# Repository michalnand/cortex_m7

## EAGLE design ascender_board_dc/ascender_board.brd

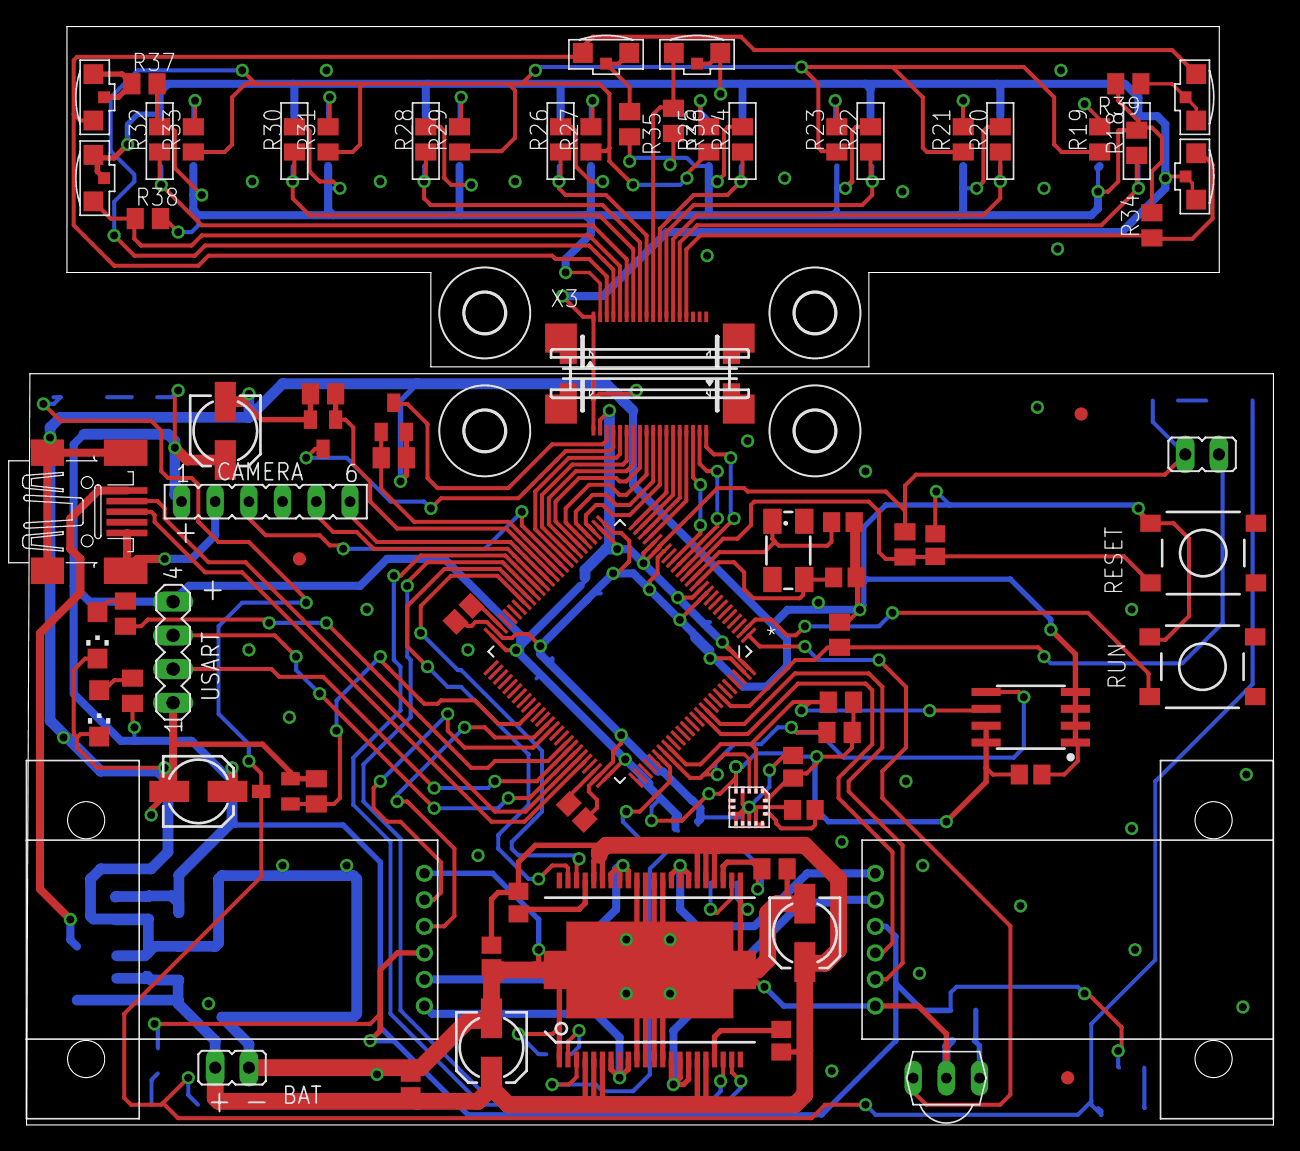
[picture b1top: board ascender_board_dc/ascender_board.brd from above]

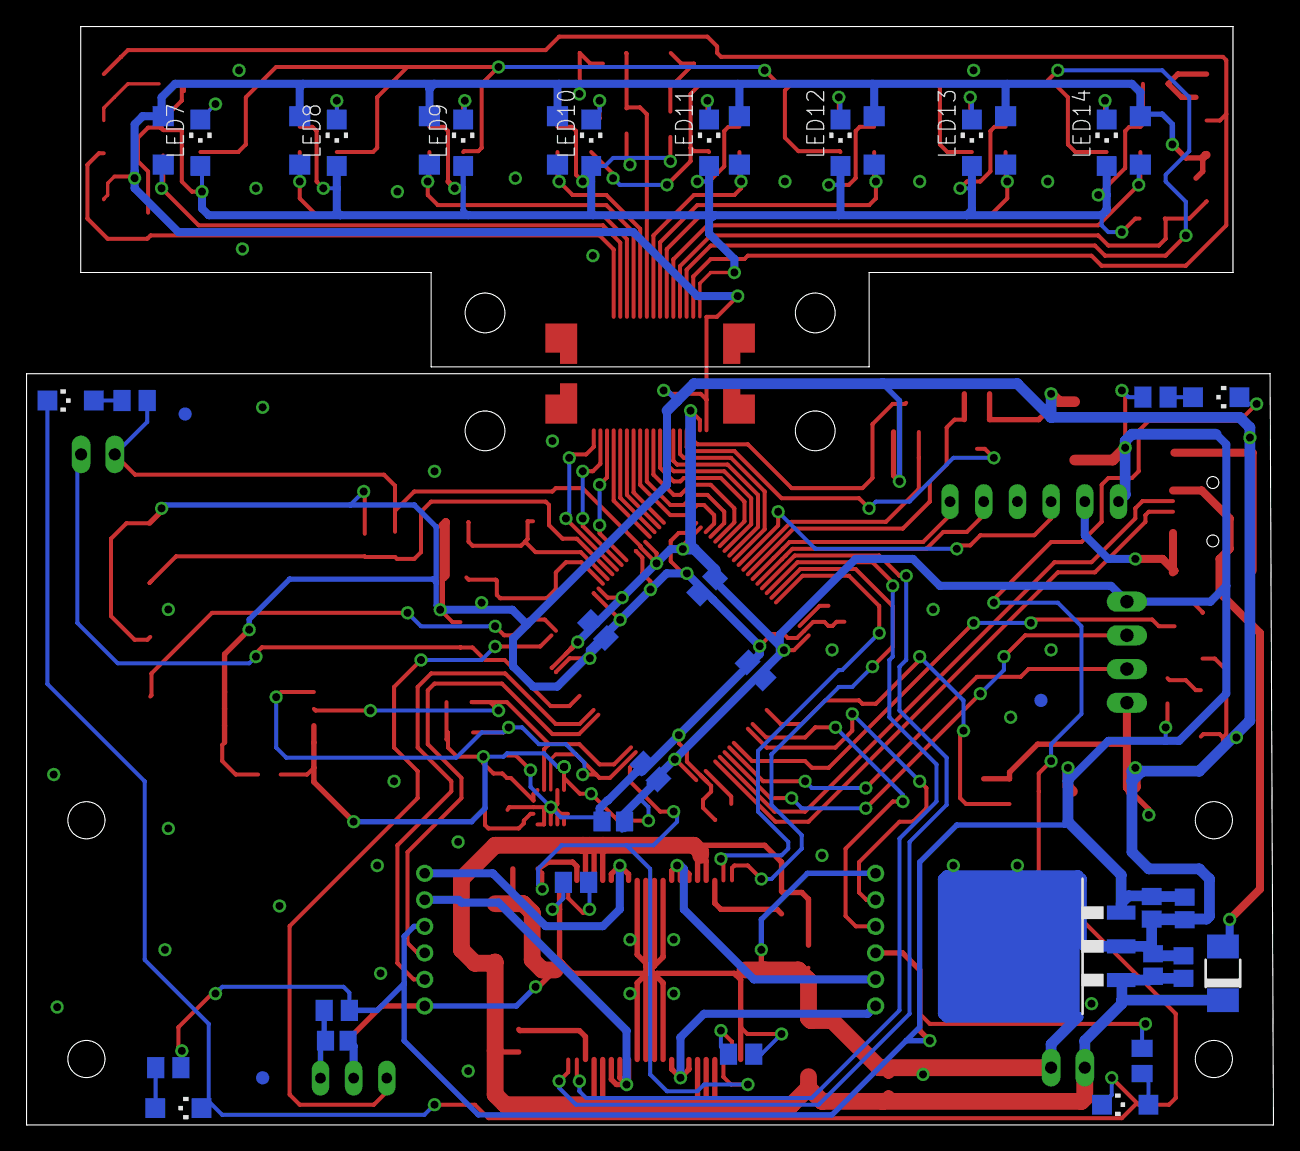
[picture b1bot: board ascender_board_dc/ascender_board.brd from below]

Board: 2 copper layers, 94.0 x 82.8 mm, 125 parts (42 on the bottom side), 91 nets.

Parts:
BAT: LiPol; JP1
BOOT: JP1
C1: C0805
C2: 18p; C0805
C3, C6, C7, C8, C9, C10, C12, C15, C16, C17, C18, C19, C23, C26: 100n; C0805
C4, C5: 2.2uF; C0805
C11, C13, C25: 10uF; C0805
C14: 10n; C0805
C20, C21, C22, C24: 153CLV-0505
CAMERA: FE06
D1: DO-214AC
H1, H2, H3, H4: MOUNT-HOLE3.0; 3,0
IC1: LM2937; TO263-3
IC2: MC33932; HSOP44
LED1, LED2, LED3, LED4, LED5, LED6, LED7, LED8, LED9, LED10, LED11, LED12, LED13, LED14: CHIPLED_1206
Q1: 8MHz; CTS406
Q2, Q3, Q4: BSS123; SOT23
R1, R2, R3, R4, R5, R6, R7, R8, R9, R10, R11, R12, R18, R20, R22, R24, R26, R28, R30, R32, R34, R36, R38: 4k7; M0805
R13, R14, R15, R16, R19, R21, R23, R25, R27, R29, R31, R33: 330; M0805
R17, R35, R37, R39: 22; M0805
RESET: DTSM-6
RUN: DTSM-6
U1: STM32F722XX; QFP50P1600X1600X160-100N
U2: I2C EEPROM; SO08-EIAJ
U$1, U$10: POLOLU_GEAR_MOTORPOLO; POLOLU_GEAR_MOTOR
U$2: ST_L3GD20H; ST_LGA16L
U$3, U$4, U$5, U$6, U$7, U$8: FIDUCIAL; FIDUCIAL_1MM
U$9: TSOP4830; TSOP18XX
U$11, U$14, U$15, U$16, U$17, U$18, U$19, U$20: SFH3710
U$12, U$29, U$31: KPA3010
U$13, U$30, U$32: KPA3010_EM; KPA3010
USART: MA04-1
X2, X3: 52745-1890
X4: MINI-USB-SCHIELD-32005-201; 32005-201

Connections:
+3V3: BOOT.2, C6.1, C7.1, C8.1, C9.1, C12.1, C13.1, C15.1, C16.1, C22.+, C24.+, C26.1, CAMERA.1, IC1.3, LED7.A, LED8.A, LED9.A, LED10.A, LED11.A, LED12.A, LED13.A, LED14.A, R1.2, R4.2, R5.2, R6.2, R13.2, R14.2, R15.2, R16.2, R17.2, R18.2, R20.2, R22.2, R24.2, R26.2, R28.2, R30.2, R32.2, R34.2, R35.2, R36.2, R37.2, R38.2, R39.2, U1.11, U1.20, U1.21, U1.27, U1.50, U1.75, U1.100, U2.7, U2.8, U$1.P$3, U$2.P$1, U$2.P$5, U$2.P$16, U$10.P$3, USART.4, X2.17, X3.2
ADC0: U1.22, X2.4
ADC1: U1.23, X2.5
ADC1_S: R18.1, U$11.P$2, X3.14
ADC2: U1.24, X2.6
ADC2_S: R20.1, U$14.P$2, X3.13
ADC3: U1.25, X2.7
ADC3_S: R22.1, U$15.P$2, X3.12
ADC4: U1.28, X2.8
ADC4_S: R24.1, U$16.P$2, X3.11
ADC5: U1.29, X2.9
ADC6: U1.30, X2.10
ADC6_S: R26.1, U$17.P$2, X3.9
ADC7: U1.31, X2.11
ADC7_S: R28.1, U$18.P$2, X3.8
ADC8: U1.32, X2.12
ADC8_S: R30.1, U$19.P$2, X3.7
ADC9: U1.33, X2.13
ADC9_S: R32.1, U$20.P$2, X3.6
ADC10: U1.34, X2.14
ADC11: CAMERA.3, U1.35
BOOT: BOOT.1, R2.2, U1.94
CAM_CLK: CAMERA.5, U1.39
CAM_SI: CAMERA.6, U1.38
ENC_A_LEFT: U1.63, U$10.P$4
ENC_A_RIGHT: U1.90, U$1.P$4
ENC_B_LEFT: U1.64, U$10.P$5
ENC_B_RIGHT: U1.91, U$1.P$5
FRONT_GPIO: U1.17, X2.3
FRONT_SCL: U1.15, X2.1
FRONT_SDA: U1.16, X2.2
GND: BAT.1, C1.2, C2.2, C3.2, C4.2, C5.1, C6.2, C7.2, C8.2, C9.2, C10.2, C11.2, C12.2, C13.2, C14.2, C15.2, C16.2, C19.2, C20.-, C21.-, C22.-, C23.2, C24.-, C25.2, C26.2, CAMERA.2, IC1.2, IC2.1, IC2.10, IC2.11, IC2.12, IC2.13, IC2.23, IC2.32, IC2.33, IC2.34, IC2.35, IC2.EH@1, IC2.EH@2, IC2.EH@3, LED1.C, LED2.C, Q2.2, Q3.2, Q4.2, R2.1, R7.1, R8.1, R9.2, R10.1, R11.1, R12.1, RESET.1, RUN.1, U1.10, U1.19, U1.26, U1.49, U1.74, U1.99, U2.1, U2.2, U2.3, U2.4, U$1.P$6, U$2.P$4, U$2.P$8, U$2.P$9, U$2.P$10, U$2.P$11, U$2.P$12, U$2.P$13, U$2.P$15, U$9.GND, U$10.P$6, U$11.P$1, U$12.P$2_EM, U$12.P$3-NC, U$14.P$1, U$15.P$1, U$16.P$1, U$17.P$1, U$18.P$1, U$19.P$1, U$20.P$1, U$29.P$2_EM, U$29.P$3-NC, U$31.P$2_EM, U$31.P$3-NC, USART.1, X2.18, X3.1, X4.5, X4.M1, X4.M2, X4.M3, X4.M4
IR_A: Q2.3, X2.15
IR_A_CONTROLL: Q2.1, R10.2, U1.37
IR_A_S: R19.1, R21.1, R23.1, R25.1, R27.1, R29.1, R31.1, R33.1, X3.4
IR_B: Q3.3, X2.16
IR_B_CONTROLL: Q3.1, R11.2, U1.36
IR_B_S: U$13.P$1_COL, U$30.P$1_COL, U$32.P$1_COL, X3.3
IR_FRONT_S: R36.1, U$29.P$1_COL, X3.10
IR_LEFT_S: R38.1, U$31.P$1_COL, X3.5
IR_REMOTE: U1.1, U$9.OUT
IR_RIGHT_S: R34.1, U$12.P$1_COL, X3.15
KEY: RUN.3, U1.2
LED: R3.2, U1.67
LED_BACK: Q4.1, R12.2, U1.60
MOTOR_ENABLE: IC2.3, IC2.25, R7.2, U1.81
unnamed: C2.1, Q1.3, U1.12
unnamed: C1.1, Q1.1, U1.13
unnamed: C4.1, U1.48
unnamed: C5.2, U1.73
unnamed: LED1.A, R3.1
unnamed: C14.1, U$2.P$14
unnamed: IC2.7, IC2.8, IC2.9, U$10.P$1
unnamed: IC2.36, IC2.37, IC2.38, U$10.P$2
unnamed: IC2.14, IC2.15, IC2.16, U$1.P$2
unnamed: IC2.29, IC2.30, IC2.31, U$1.P$1
unnamed: LED2.A, R6.1
unnamed: C17.2, IC2.41
unnamed: IC2.2, R8.2
unnamed: C18.1, IC2.19
unnamed: IC2.24, R9.1
unnamed: LED3.C, LED4.C, LED5.C, LED6.C, Q4.3
unnamed: LED3.A, R13.1
unnamed: D1.A, X4.1
unnamed: LED4.A, R14.1
unnamed: C25.1, R17.1, U$9.VCC
unnamed: LED5.A, R15.1
unnamed: LED8.C, R21.2
unnamed: LED6.A, R16.1
unnamed: LED7.C, R19.2
unnamed: LED9.C, R23.2
unnamed: LED10.C, R25.2
unnamed: LED11.C, R27.2
unnamed: LED12.C, R29.2
unnamed: LED13.C, R31.2
unnamed: LED14.C, R33.2
unnamed: R37.1, U$30.P$2_EM, U$30.P$3-NC
unnamed: R35.1, U$13.P$2_EM, U$13.P$3-NC
unnamed: R39.1, U$32.P$2_EM, U$32.P$3-NC
PWM_A_LEFT: IC2.43, U1.42
PWM_A_RIGHT: IC2.21, U1.40
PWM_B_LEFT: IC2.42, U1.43
PWM_B_RIGHT: IC2.20, U1.41
RESET: C3.1, R1.1, RESET.3, U1.14
SCL: R5.1, U1.83, U2.6, U$2.P$2
SDA: R4.1, U1.82, U2.5, U$2.P$3
USART1_RX: U1.69, USART.3
USART1_TX: U1.68, USART.2
USBDM: U1.70, X4.2
USBDP: U1.71, X4.3
VCC: BAT.2, C10.1, C11.1, C17.1, C18.2, C19.1, C20.+, C21.+, C23.1, D1.C, IC1.1, IC2.4, IC2.5, IC2.6, IC2.17, IC2.18, IC2.26, IC2.27, IC2.28, IC2.39, IC2.40

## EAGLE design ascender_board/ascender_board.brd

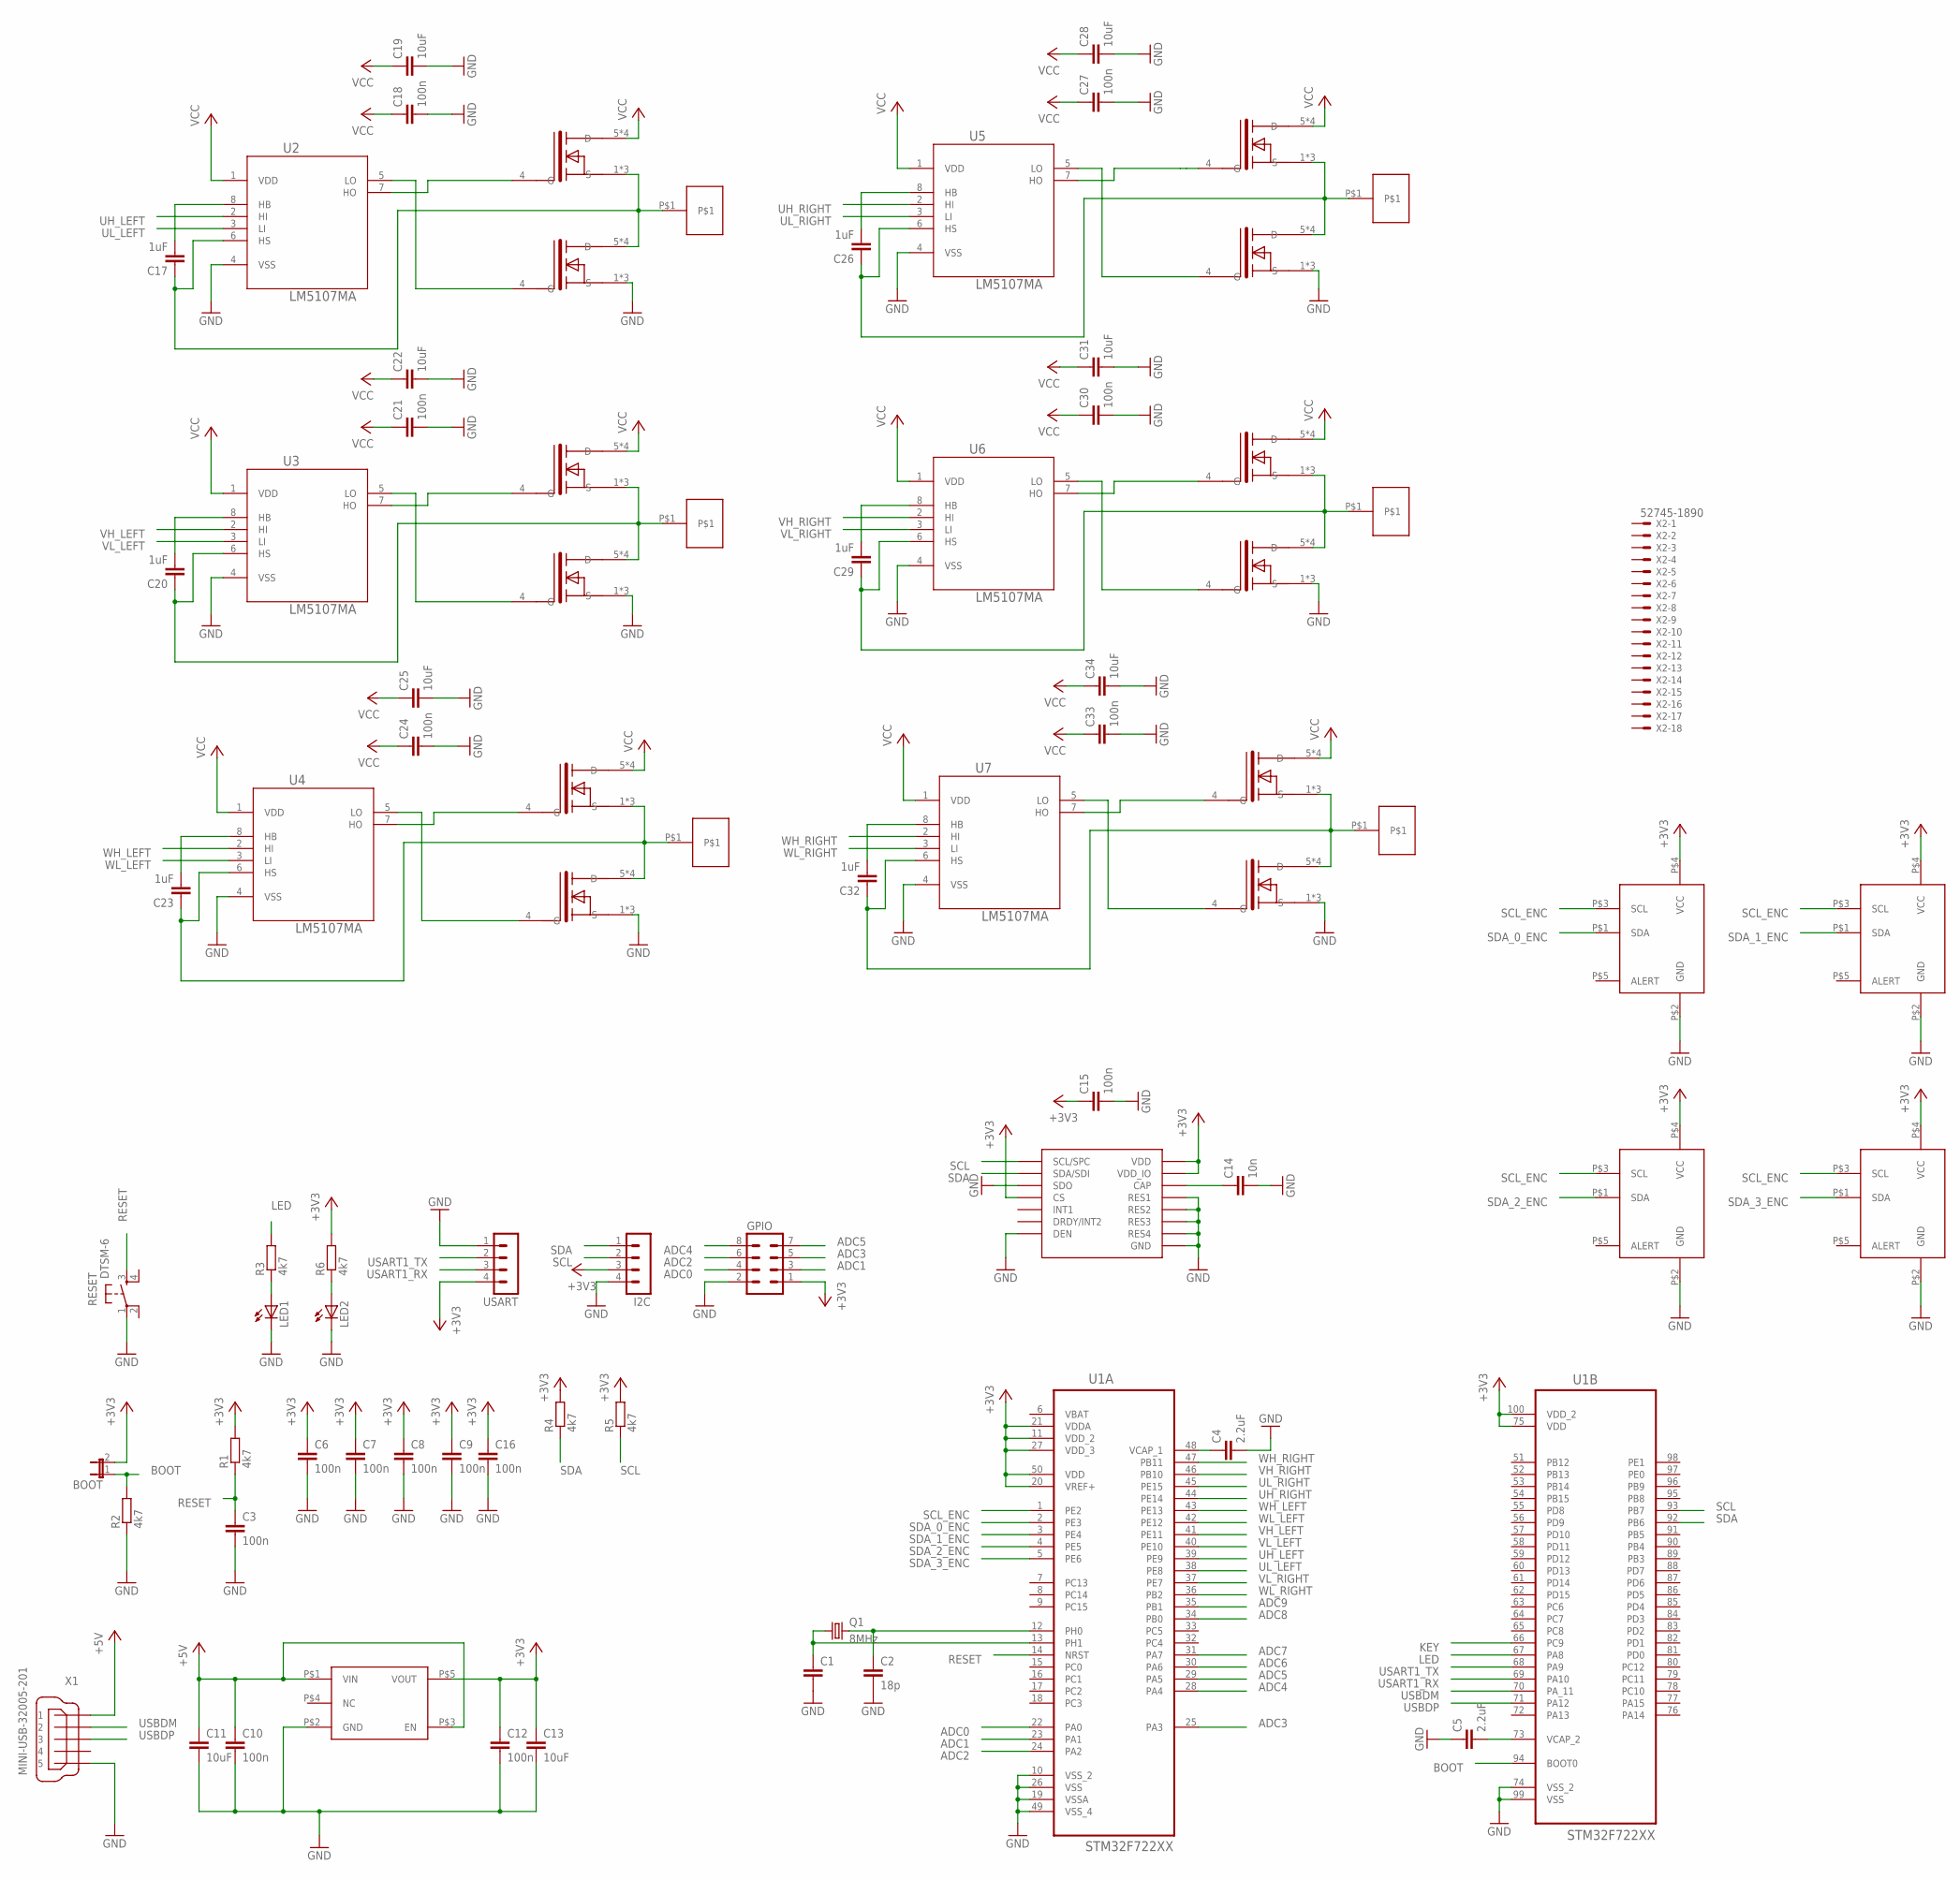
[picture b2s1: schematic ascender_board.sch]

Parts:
BOOT: JP1E; JP1
C1: C-EUC0805; C0805
C2: 18p; C0805
C3, C6, C7, C8, C9, C10, C12, C15, C16, C18, C21, C24, C27, C30, C33: 100n; C0805
C4, C5: 2.2uF; C0805
C11, C13, C19, C22, C25, C28, C31, C34: 10uF; C0805
C14: 10n; C0805
C17, C20, C23, C26, C29, C32: 1uF; C0805
GPIO: MA04-2
I2C: MA04-1
LED1, LED2: LEDCHIPLED_1206; CHIPLED_1206
Q1: 8MHz; CTS406
R1, R2, R3, R4, R5, R6: 4k7; M0805
RESET: DTSM-6
U1: STM32F722XX; QFP50P1600X1600X160-100N
U2, U3, U4, U5, U6, U7: LM5107MA; SOIC127P620X175-8N
U$1: MIC5504-3.3Y; SOT23-5
U$2: ST_L3GD20H; ST_LGA16L
U$4, U$5, U$7, U$8, U$10, U$11, U$13, U$14, U$16, U$17, U$19, U$20: IRFH7004; PQFN5X6
U$6, U$9, U$12, U$15, U$18, U$21: BLDC_MOTOR_PIN
U$22, U$23, U$24, U$25: SI7210; SOT23-5
USART: MA04-1
X1: MINI-USB-32005-201; 32005-201
X2: 52745-1890

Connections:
+3V3: BOOT.2, C6.1, C7.1, C8.1, C9.1, C12.1, C13.1, C15.1, C16.1, GPIO.1, I2C.3, R1.2, R4.2, R5.2, R6.2, U1.11 (VDD_2), U1.20 (VREF+), U1.21 (VDDA), U1.27 (VDD_3), U1.50 (VDD), U1.75 (VDD), U1.100 (VDD_2), U$1.P$5 (VOUT), U$2.P$1 (VDD_IO), U$2.P$5 (CS), U$2.P$16 (VDD), U$22.P$4 (VCC), U$23.P$4 (VCC), U$24.P$4 (VCC), U$25.P$4 (VCC), USART.4
+5V: C10.1, C11.1, U$1.P$1 (VIN), U$1.P$3 (EN), X1.1
ADC0: GPIO.4, U1.22 (PA0)
ADC1: GPIO.3, U1.23 (PA1)
ADC2: GPIO.6, U1.24 (PA2)
ADC3: GPIO.5, U1.25 (PA3)
ADC4: GPIO.8, U1.28 (PA4)
ADC5: GPIO.7, U1.29 (PA5)
ADC6: U1.30 (PA6)
ADC7: U1.31 (PA7)
ADC8: U1.34 (PB0)
ADC9: U1.35 (PB1)
BOOT: BOOT.1, R2.2, U1.94 (BOOT0)
GND: C1.2, C2.2, C3.2, C4.2, C5.1, C6.2, C7.2, C8.2, C9.2, C10.2, C11.2, C12.2, C13.2, C14.2, C15.2, C16.2, C18.2, C19.2, C21.2, C22.2, C24.2, C25.2, C27.2, C28.2, C30.2, C31.2, C33.2, C34.2, GPIO.2, I2C.4, LED1.C, LED2.C, R2.1, RESET.1, U1.10 (VSS_2), U1.19 (VSSA), U1.26 (VSS), U1.49 (VSS_4), U1.74 (VSS_2), U1.99 (VSS), U2.4 (VSS), U3.4 (VSS), U4.4 (VSS), U5.4 (VSS), U6.4 (VSS), U7.4 (VSS), U$1.P$2 (GND), U$2.P$4 (SDO), U$2.P$8 (DEN), U$2.P$9 (RES1), U$2.P$10 (RES2), U$2.P$11 (RES3), U$2.P$12 (GND), U$2.P$13 (GND), U$2.P$15 (RES4), U$5.1 (S), U$5.2 (S), U$5.3 (S), U$8.1 (S), U$8.2 (S), U$8.3 (S), U$11.1 (S), U$11.2 (S), U$11.3 (S), U$14.1 (S), U$14.2 (S), U$14.3 (S), U$17.1 (S), U$17.2 (S), U$17.3 (S), U$20.1 (S), U$20.2 (S), U$20.3 (S), U$22.P$2 (GND), U$23.P$2 (GND), U$24.P$2 (GND), U$25.P$2 (GND), USART.1, X1.5
KEY: U1.66 (PC9)
LED: R3.2, U1.67 (PA8)
unnamed: C2.1, Q1.3 (2), U1.12 (PH0)
unnamed: C1.1, Q1.1, U1.13 (PH1)
unnamed: C4.1, U1.48 (VCAP_1)
unnamed: C5.2, U1.73 (VCAP_2)
unnamed: LED1.A, R3.1
unnamed: C14.1, U$2.P$14 (CAP)
unnamed: U3.5 (LO), U$8.4 (G)
unnamed: U2.5 (LO), U$5.4 (G)
unnamed: U2.7 (HO), U$4.4 (G)
unnamed: LED2.A, R6.1
unnamed: U3.7 (HO), U$7.4 (G)
unnamed: C17.2, U2.8 (HB)
unnamed: C17.1, U2.6 (HS), U$4.1 (S), U$4.2 (S), U$4.3 (S), U$5.5 (D), U$5.6 (D), U$5.7 (D), U$5.8 (D), U$6.P$1
unnamed: C20.2, U3.8 (HB)
unnamed: C20.1, U3.6 (HS), U$7.1 (S), U$7.2 (S), U$7.3 (S), U$8.5 (D), U$8.6 (D), U$8.7 (D), U$8.8 (D), U$9.P$1
unnamed: U4.5 (LO), U$11.4 (G)
unnamed: U4.7 (HO), U$10.4 (G)
unnamed: C23.2, U4.8 (HB)
unnamed: C23.1, U4.6 (HS), U$10.1 (S), U$10.2 (S), U$10.3 (S), U$11.5 (D), U$11.6 (D), U$11.7 (D), U$11.8 (D), U$12.P$1
unnamed: U5.5 (LO), U$14.4 (G)
unnamed: U5.7 (HO), U$13.4 (G)
unnamed: C26.2, U5.8 (HB)
unnamed: C26.1, U5.6 (HS), U$13.1 (S), U$13.2 (S), U$13.3 (S), U$14.5 (D), U$14.6 (D), U$14.7 (D), U$14.8 (D), U$15.P$1
unnamed: U6.5 (LO), U$17.4 (G)
unnamed: U6.7 (HO), U$16.4 (G)
unnamed: C29.2, U6.8 (HB)
unnamed: C29.1, U6.6 (HS), U$16.1 (S), U$16.2 (S), U$16.3 (S), U$17.5 (D), U$17.6 (D), U$17.7 (D), U$17.8 (D), U$18.P$1
unnamed: U7.5 (LO), U$20.4 (G)
unnamed: U7.7 (HO), U$19.4 (G)
unnamed: C32.2, U7.8 (HB)
unnamed: C32.1, U7.6 (HS), U$19.1 (S), U$19.2 (S), U$19.3 (S), U$20.5 (D), U$20.6 (D), U$20.7 (D), U$20.8 (D), U$21.P$1
RESET: C3.1, R1.1, RESET.3, U1.14 (NRST)
SCL: I2C.2, R5.1, U1.93 (PB7), U$2.P$2 (SCL/SPC)
SCL_ENC: U1.1 (PE2), U$22.P$3 (SCL), U$23.P$3 (SCL), U$24.P$3 (SCL), U$25.P$3 (SCL)
SDA: I2C.1, R4.1, U1.92 (PB6), U$2.P$3 (SDA/SDI)
SDA_0_ENC: U1.2 (PE3), U$22.P$1 (SDA)
SDA_1_ENC: U1.3 (PE4), U$23.P$1 (SDA)
SDA_2_ENC: U1.4 (PE5), U$24.P$1 (SDA)
SDA_3_ENC: U1.5 (PE6), U$25.P$1 (SDA)
UH_LEFT: U1.39 (PE9), U2.2 (HI)
UH_RIGHT: U1.44 (PE14), U5.2 (HI)
UL_LEFT: U1.38 (PE8), U2.3 (LI)
UL_RIGHT: U1.45 (PE15), U5.3 (LI)
USART1_RX: U1.69 (PA10), USART.3
USART1_TX: U1.68 (PA9), USART.2
USBDM: U1.70 (PA_11), X1.2
USBDP: U1.71 (PA12), X1.3
VBAT: U1.6 (VBAT)
VCC: C18.1, C19.1, C21.1, C22.1, C24.1, C25.1, C27.1, C28.1, C30.1, C31.1, C33.1, C34.1, U2.1 (VDD), U3.1 (VDD), U4.1 (VDD), U5.1 (VDD), U6.1 (VDD), U7.1 (VDD), U$4.5 (D), U$4.6 (D), U$4.7 (D), U$4.8 (D), U$7.5 (D), U$7.6 (D), U$7.7 (D), U$7.8 (D), U$10.5 (D), U$10.6 (D), U$10.7 (D), U$10.8 (D), U$13.5 (D), U$13.6 (D), U$13.7 (D), U$13.8 (D), U$16.5 (D), U$16.6 (D), U$16.7 (D), U$16.8 (D), U$19.5 (D), U$19.6 (D), U$19.7 (D), U$19.8 (D)
VH_LEFT: U1.41 (PE11), U3.2 (HI)
VH_RIGHT: U1.46 (PB10), U6.2 (HI)
VL_LEFT: U1.40 (PE10), U3.3 (LI)
VL_RIGHT: U1.37 (PE7), U6.3 (LI)
WH_LEFT: U1.43 (PE13), U4.2 (HI)
WH_RIGHT: U1.47 (PB11), U7.2 (HI)
WL_LEFT: U1.42 (PE12), U4.3 (LI)
WL_RIGHT: U1.36 (PB2), U7.3 (LI)

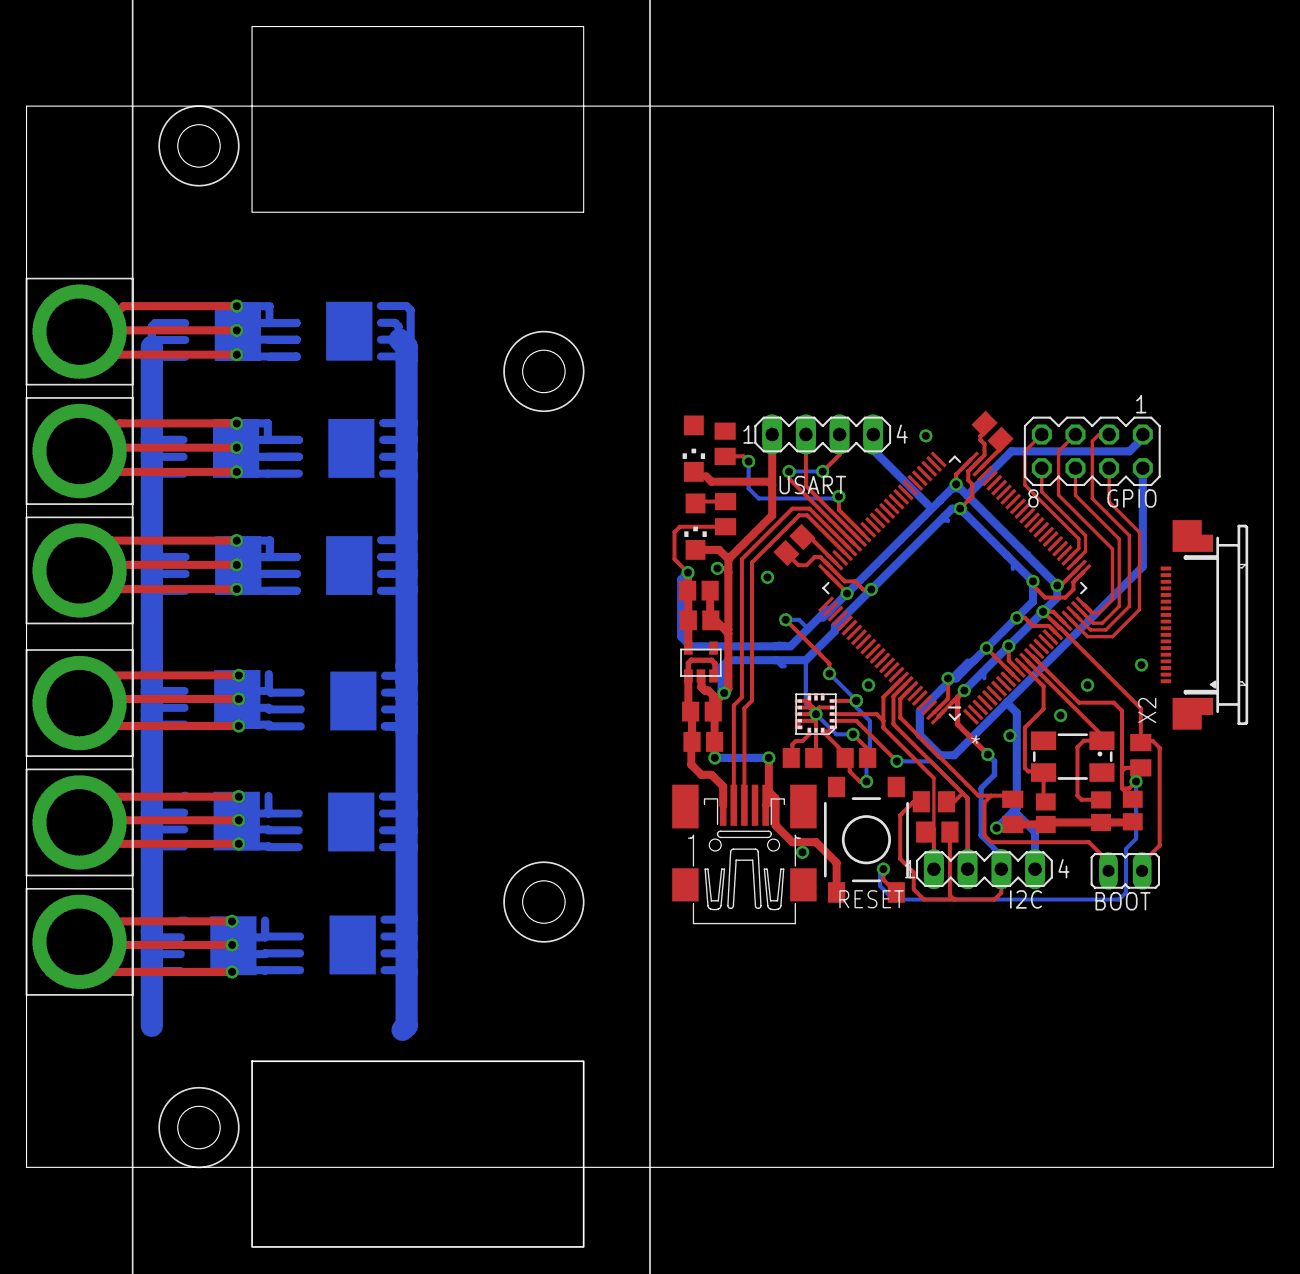
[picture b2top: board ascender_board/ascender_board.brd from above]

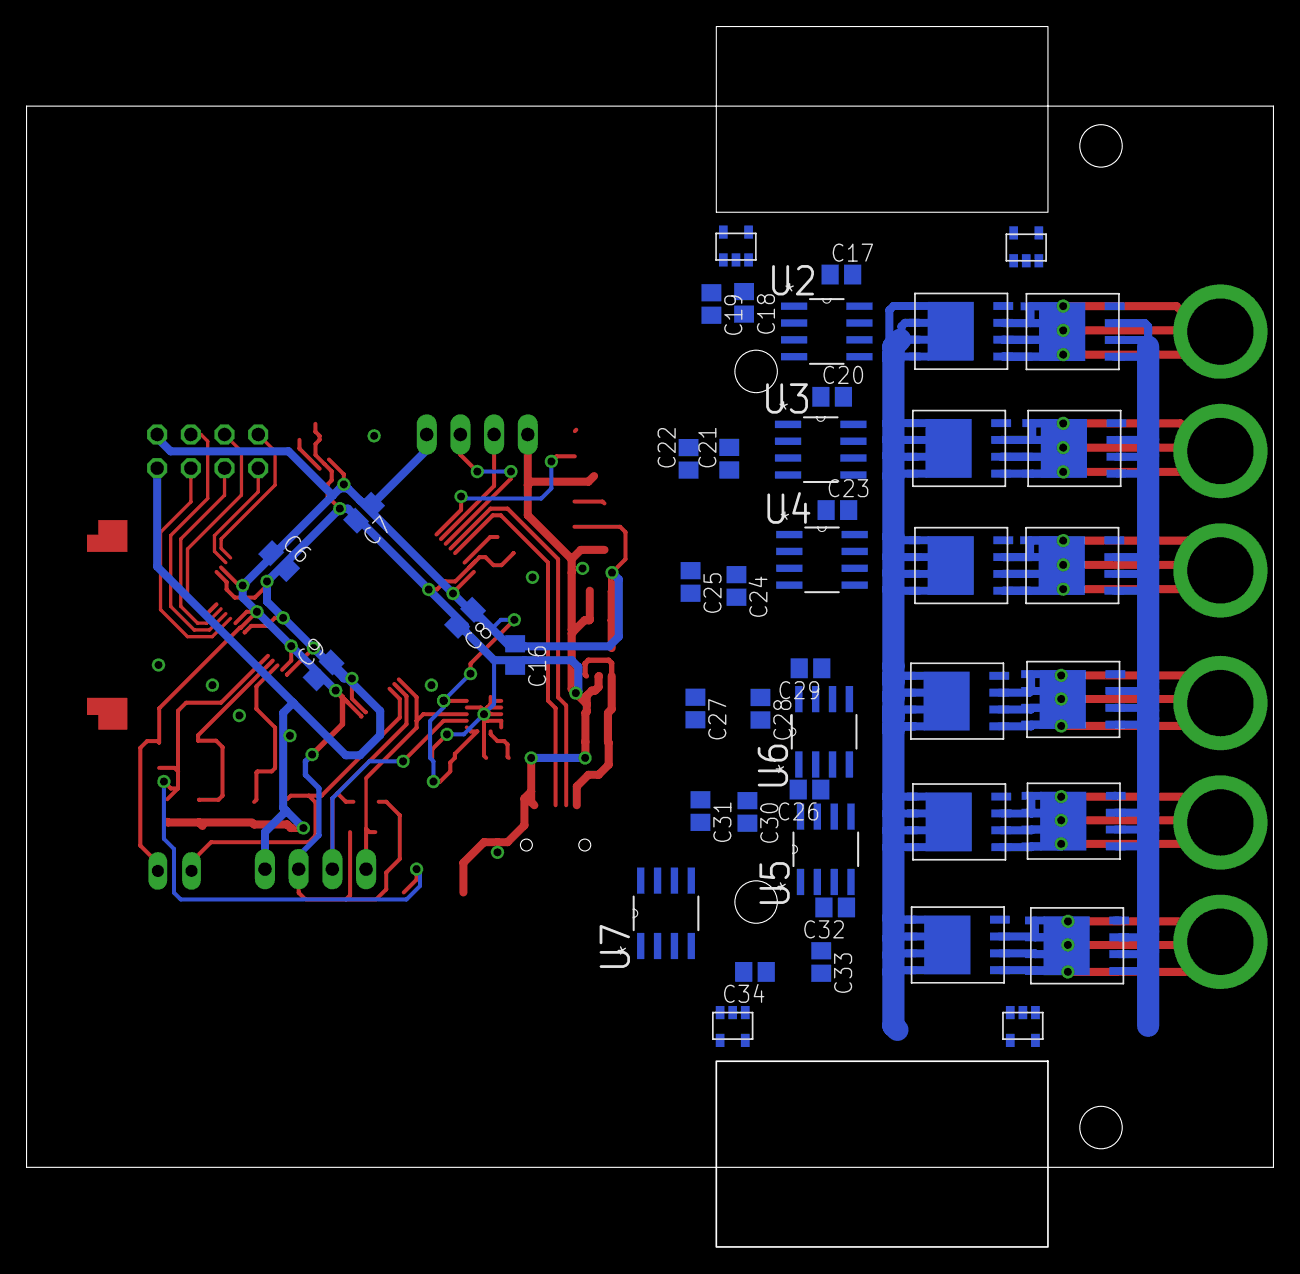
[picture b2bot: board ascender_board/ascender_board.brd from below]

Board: 2 copper layers, 94.0 x 80.0 mm, 82 parts (45 on the bottom side), 67 nets.

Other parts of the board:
U$3: BLDC_MOTOR_HOLDER

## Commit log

2017-09-22 common
2017-09-24 dfu usb
2017-09-30 camera
2017-09-30 edge detector
2017-10-04 board
2017-10-06 terminal, operator <<
2017-10-08 mess in kodama cleaned up
2017-10-22 wave
2017-12-18 ir cam
2018-01-28 touch
2018-01-28 neural network demo
2018-08-11 dense net

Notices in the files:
parts and their libraries:
SparkFun-IC-Memory: Licensing: Creative Commons ShareAlike 4.0 International - https://creativecommons.org/licenses/by-sa/4.0
